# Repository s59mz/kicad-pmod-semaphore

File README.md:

# kicad-pmod-semaphore
Just a simple push-buttons and LEDs PMOD module

Schematic:
[kicad-pmod-semaphore.pdf](kicad-pmod-semaphore.pdf)

BOM:
[kicad-pmod-semaphore.csv](kicad-pmod-semaphore.csv)

Gerbers:
[gerbers.zip](https://github.com/s59mz/kicad-pmod-semaphore/raw/main/gerbers.zip)

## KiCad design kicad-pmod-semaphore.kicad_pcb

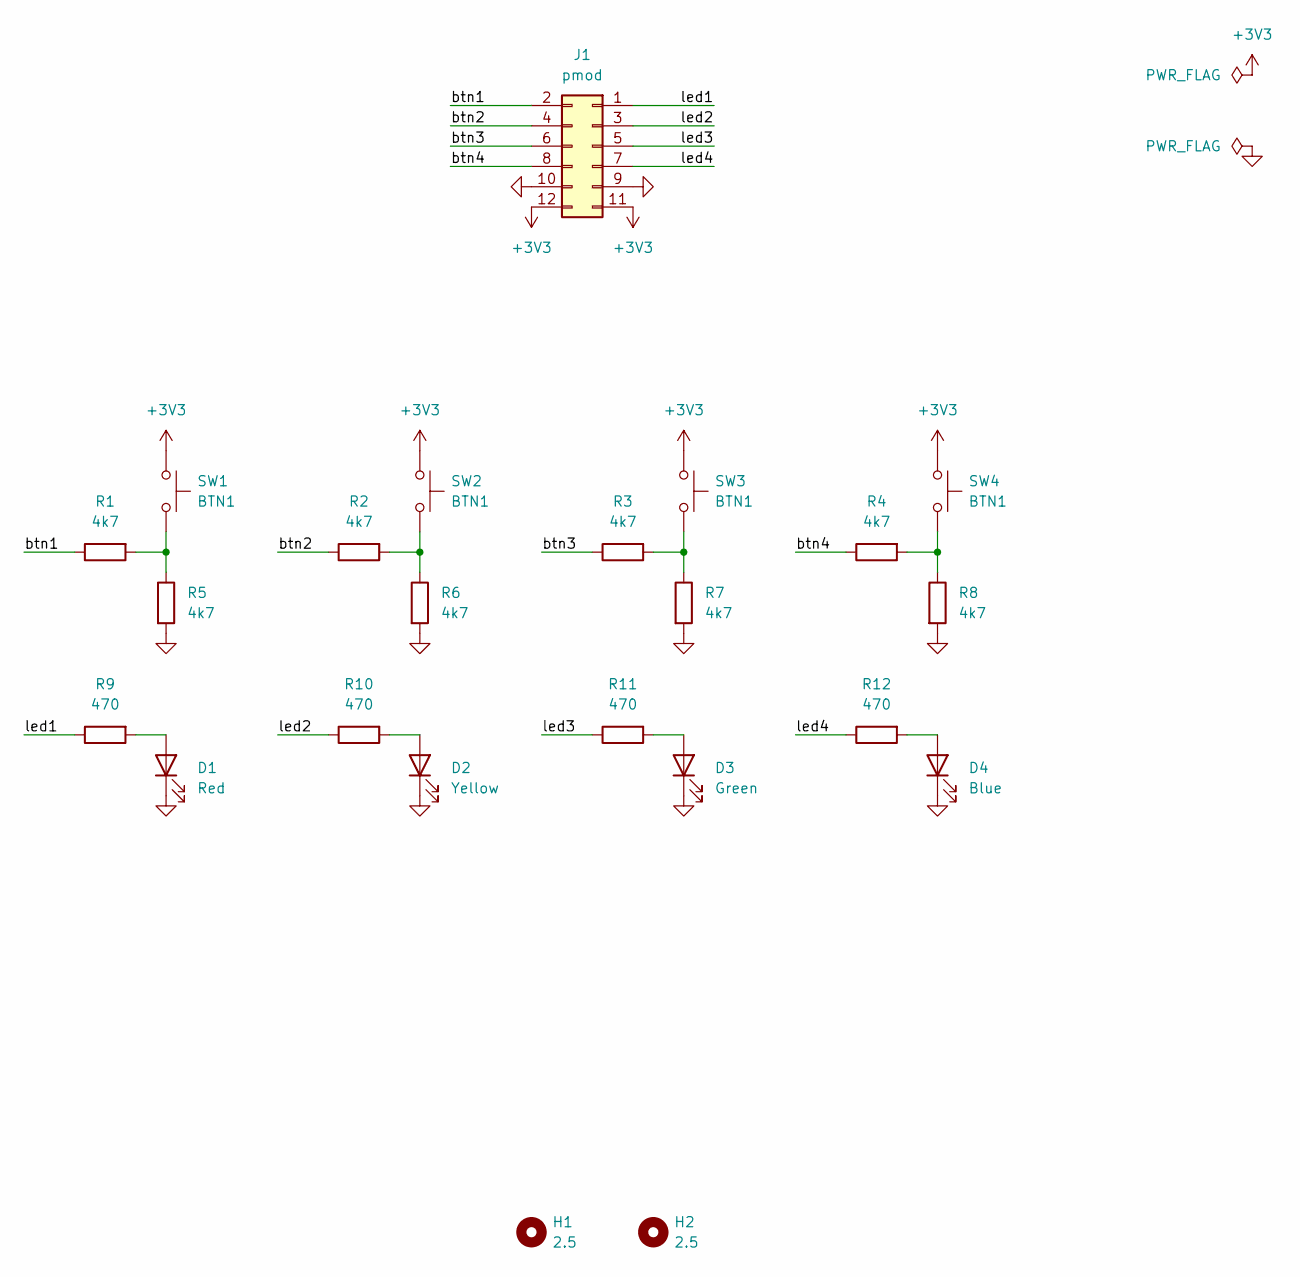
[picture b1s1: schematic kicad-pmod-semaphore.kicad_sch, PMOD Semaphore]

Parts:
D1: Red; LED_D5.0mm
D2: Yellow; LED_D5.0mm
D3: Green; LED_D5.0mm
D4: Blue; LED_D5.0mm_Clear
H1, H2: 2.5; MountingHole_2.5mm
J1: pmod; PinHeader_2x06_P2.54mm_Horizontal
R1, R2, R3, R4, R5, R6, R7, R8: 4k7; R_0603_1608Metric_Pad0.98x0.95mm_HandSolder
R9, R10, R11, R12: 470; R_0603_1608Metric_Pad0.98x0.95mm_HandSolder
SW1, SW2, SW3, SW4: BTN1; SW_PUSH_6mm

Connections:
+3V3: J1.11, J1.12, SW1.1, SW2.1, SW3.1, SW4.1
/btn1: J1.2, R1.1
/btn2: J1.4, R2.1
/btn3: J1.6, R3.1
/btn4: J1.8, R4.1
/led1: J1.1, R9.1
/led2: J1.3, R10.1
/led3: J1.5, R11.1
/led4: J1.7, R12.1
GND: D1.1 (K), D2.1 (K), D3.1 (K), D4.1 (K), J1.9, J1.10, R5.2, R6.2, R7.2, R8.2
unnamed: D1.2 (A), R9.2
unnamed: D2.2 (A), R10.2
unnamed: D3.2 (A), R11.2
unnamed: D4.2 (A), R12.2
unnamed: R1.2, R5.1, SW1.2
unnamed: R2.2, R6.1, SW2.2
unnamed: R3.2, R7.1, SW3.2
unnamed: R4.2, R8.1, SW4.2

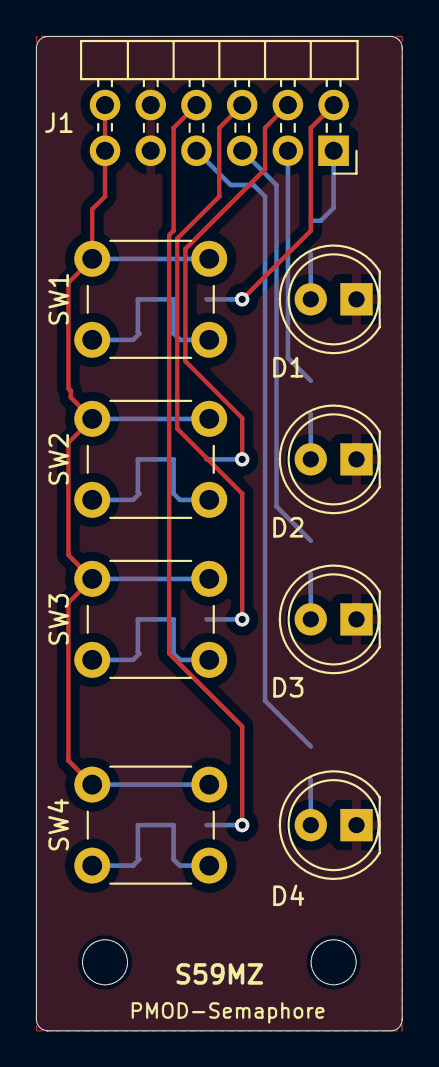
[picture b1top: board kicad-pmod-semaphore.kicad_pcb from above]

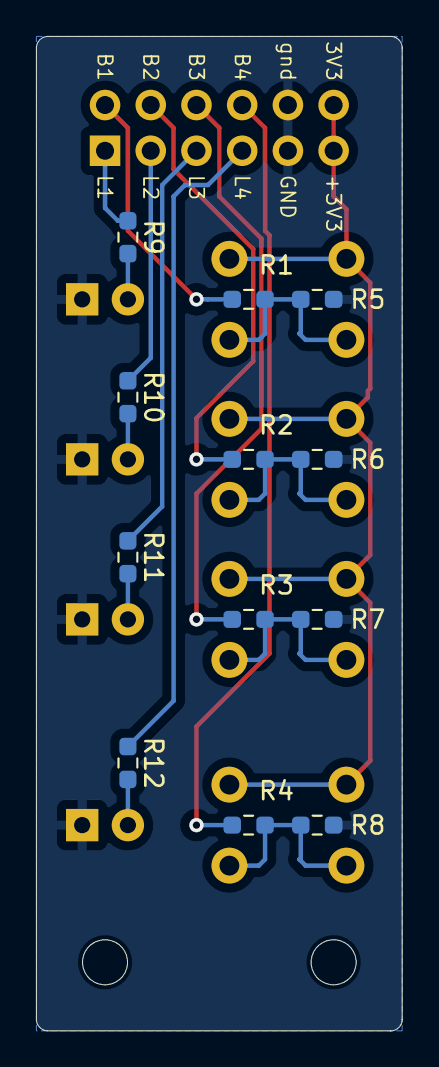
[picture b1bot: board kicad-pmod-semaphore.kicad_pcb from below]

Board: 2 copper layers, 20.3 x 55.2 mm, 23 parts (12 on the bottom side), 18 nets.
